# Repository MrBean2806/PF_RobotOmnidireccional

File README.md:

# PF_RobotOmnidireccional
## Proyecto Final de Grado - Ingeniería Electrónica
## _"Sistema de Control de Tracción de Bajo Nivel para un Robot Móvil"_

<div style="text-align: center;">
  
</div>

### Introducción
El proyecto se centra en el desarrollo de un sistema de control de tracción de bajo nivel para un robot móvil. Su principal objetivo es transformar los comandos de velocidad provenientes de la Computadora de Navegación en velocidades individuales para cada motor. Además, el sistema ejecuta un lazo de control de
velocidad en cada rueda, midiendo y ajustando la tensión media aplicada a cada motor. Finalmente, el sistema envía datos de velocidad estimada y aceleración a
la Computadora de Navegación. 

Este proyecto forma parte de una iniciativa más amplia del Centro Universitario
de Automatización y Robótica (CUDAR) de la UTN FRC, que abarca el diseño, desarrollo y construcción de un sistema de odometría multi-cámara montado en
un robot móvil, destinado a encontrar trayectorias eficientes en ambientes desconocidos y dinámicos.

### Contexto
A continuación se presenta el diagrama de contexto del sistema, que muestra
las entidades externas con las que éste interactúa y la naturaleza de dichas interacciones.

<div style="text-align: center;">
  
</div>

Puede observarse que el sistema interactúa directamente con las siguientes entidades externas:
La Computadora de navegación (CDN), que provee la velocidad comandada y recibe la velocidad estimada y la aceleración medida por el Controlador de Bajo Nivel (CBN).
La gravedad y la aceleración, que son medidas para el uso de la Computadora de Navegación.
Los Motores del robot móvil, cuya velocidad es seteada y medida por el sistema.

### Arquitectura de Software

En la siguiente figura se muestra el diagrama conceptual de este proyecto, en el cual se pueden apreciar dos caminos principales.

<div style="text-align: center;">
  
</div>

En primer lugar, la velocidad comandada es enviada por la CDN y recibida por el CBN, la cual es convertida en comandos de velocidad para cada motor y finalmente se envía una señal para controlar los motores, teniendo en cuenta el valor de la velocidad medida de estos últimos. 

En segunda instancia, se miden tanto los valores de velocidad de cada motor, como los valores de aceleraciones del robot, los cuales son enviados finalmente al CDN.

_Para una explicación más detallada referirse al informe completo en la carpeta "Informe"_

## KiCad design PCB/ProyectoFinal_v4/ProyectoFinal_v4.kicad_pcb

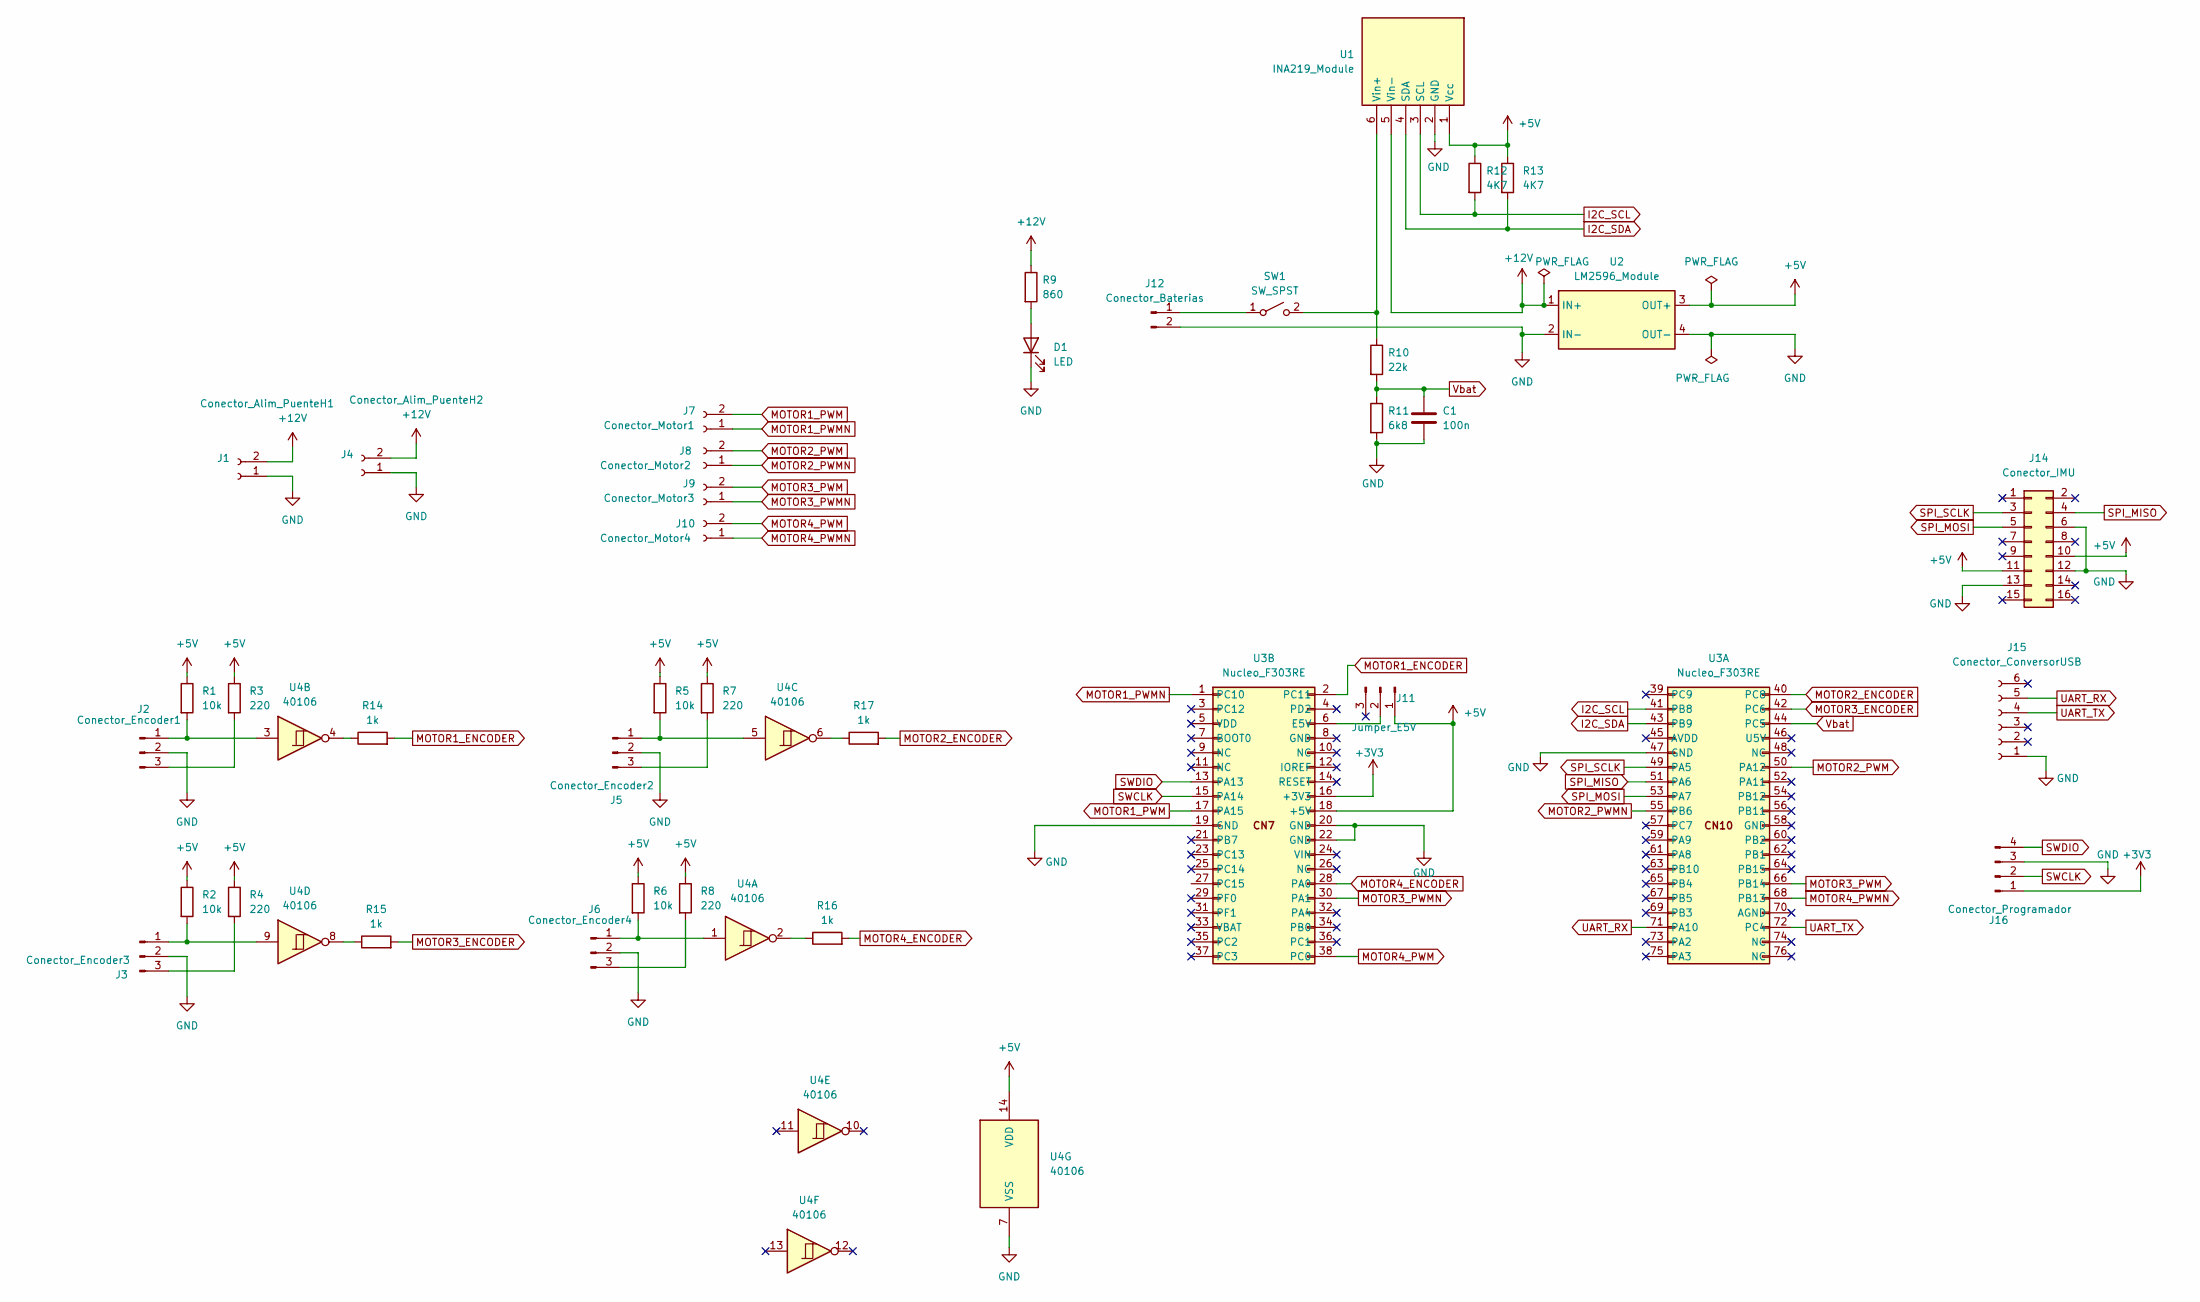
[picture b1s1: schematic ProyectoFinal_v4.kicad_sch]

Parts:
C1: 100n; C_Disc_D4.3mm_W1.9mm_P5.00mm
D1: LED; LED_D5.0mm
J1: Conector_Alim_PuenteH1; JST_EH_B2B-EH-A_1x02_P2.50mm_Vertical
J2: Conector_Encoder1; JST_EH_B3B-EH-A_1x03_P2.50mm_Vertical
J3: Conector_Encoder3; JST_EH_B3B-EH-A_1x03_P2.50mm_Vertical
J4: Conector_Alim_PuenteH2; JST_EH_B2B-EH-A_1x02_P2.50mm_Vertical
J5: Conector_Encoder2; JST_EH_B3B-EH-A_1x03_P2.50mm_Vertical
J6: Conector_Encoder4; JST_EH_B3B-EH-A_1x03_P2.50mm_Vertical
J7: Conector_Motor1; PinHeader_1x02_P2.54mm_Vertical
J8: Conector_Motor2; PinHeader_1x02_P2.54mm_Vertical
J9: Conector_Motor3; PinHeader_1x02_P2.54mm_Vertical
J10: Conector_Motor4; PinHeader_1x02_P2.54mm_Vertical
J11: Jumper_E5V; PinHeader_1x03_P2.54mm_Vertical
J12: Conector_Baterias; JST_EH_B2B-EH-A_1x02_P2.50mm_Vertical
J14: Conector_IMU
J15: Conector_ConversorUSB; PinSocket_1x06_P2.54mm_Horizontal
J16: Conector_Programador; PinSocket_1x04_P2.54mm_Vertical
R1, R2, R5, R6: 10k; R_Axial_Custom
R3, R4, R7, R8: 220; R_Axial_Custom
R9: 860; R_Axial_Custom
R10: 22k; R_Axial_Custom
R11: 6k8; R_Axial_Custom
R12, R13: 4K7; R_Axial_Custom
R14, R15, R16, R17: 1k; R_Axial_Custom
SW1: SW_SPST
U1: INA219_Module
U2: LM2596_Module; DCDC_StepDown_LM2596
U3: Nucleo_F303RE
U4: 40106; DIP-14_W7.62mm_LongPads

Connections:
+3V3: J16.1, U3.16 (+3V3)
+5V: J11.1, J14.10, J14.11, R1.1, R2.1, R3.1, R4.1, R5.1, R6.1, R7.1, R8.1, R12.1, R13.1, U1.1 (Vcc), U2.3 (OUT+), U3.18 (+5V), U4.14 (VDD)
+12V: J1.2, J4.2, R9.1, U1.5 (Vin-), U2.1 (IN+)
GND: C1.2, D1.1 (K), J1.1, J2.2, J3.2, J4.1, J5.2, J6.2, J12.2, J14.6, J14.12, J14.13, J15.1, J16.3, R11.2, U1.2 (GND), U2.2 (IN-), U2.4 (OUT-), U3.19 (GND), U3.20 (GND), U3.22 (GND), U3.47 (GND), U4.7 (VSS)
I2C_SCL: R12.2, U1.3 (SCL), U3.41 (PB8)
I2C_SDA: R13.2, U1.4 (SDA), U3.43 (PB9)
MOTOR1_ENCODER: R14.2, U3.2 (PC11)
MOTOR1_PWM: J7.2, U3.17 (PA15)
MOTOR1_PWMN: J7.1, U3.1 (PC10)
MOTOR2_ENCODER: R17.2, U3.40 (PC8)
MOTOR2_PWM: J8.2, U3.50 (PA12)
MOTOR2_PWMN: J8.1, U3.55 (PB6)
MOTOR3_ENCODER: R15.2, U3.42 (PC6)
MOTOR3_PWM: J9.2, U3.66 (PB14)
MOTOR3_PWMN: J9.1, U3.30 (PA1)
MOTOR4_ENCODER: R16.2, U3.28 (PA0)
MOTOR4_PWM: J10.2, U3.38 (PC0)
MOTOR4_PWMN: J10.1, U3.68 (PB13)
unnamed: D1.2 (A), R9.2
unnamed: J2.1, R1.2, U4.3
unnamed: J2.3, R3.2
unnamed: J3.1, R2.2, U4.9
unnamed: J3.3, R4.2
unnamed: J5.1, R5.2, U4.5
unnamed: J5.3, R7.2
unnamed: J6.1, R6.2, U4.1
unnamed: J6.3, R8.2
unnamed: J11.2, U3.6 (E5V)
unnamed: J12.1, SW1.1 (A)
unnamed: R10.1, SW1.2 (B), U1.6 (Vin+)
unnamed: R14.1, U4.4
unnamed: R15.1, U4.8
unnamed: R16.1, U4.2
unnamed: R17.1, U4.6
SPI_MISO: J14.4, U3.51 (PA6)
SPI_MOSI: J14.5, U3.53 (PA7)
SPI_SCLK: J14.3, U3.49 (PA5)
SWCLK: J16.2, U3.15 (PA14)
SWDIO: J16.4, U3.13 (PA13)
UART_RX: J15.5, U3.71 (PA10)
UART_TX: J15.4, U3.72 (PC4)
Vbat: C1.1, R10.2, R11.1, U3.44 (PC5)

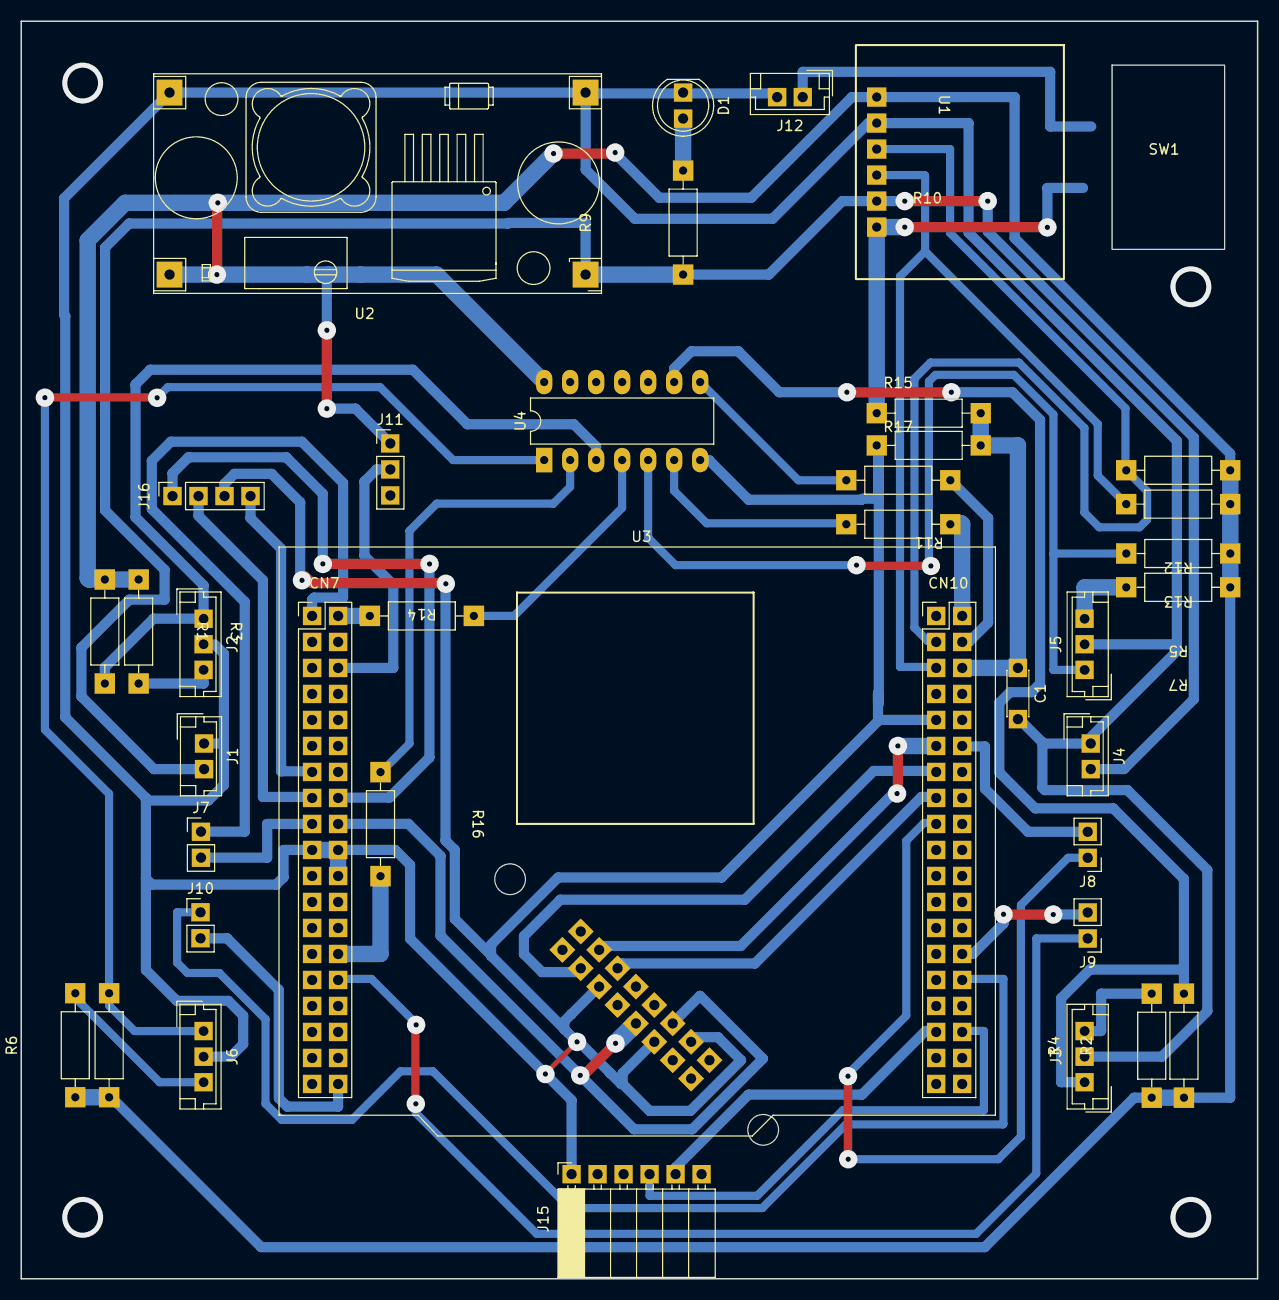
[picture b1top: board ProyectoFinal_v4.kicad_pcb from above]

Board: 2 copper layers, 120.8 x 122.8 mm, 39 parts (1 on the bottom side), 42 nets.

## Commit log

2025-02-27 Agrego codigo final del CBN
2025-02-27 Agrego archivos del PCB y del informe
2025-02-27 Agrego Datasheets
2025-03-02 Actualizo README
2025-10-07 Saco verificación de CRC en trama. Cambio pines de la UART a PB10 y PB11 (USART3)
2025-11-06 Soluciono bug en el limitador del controlador PI
